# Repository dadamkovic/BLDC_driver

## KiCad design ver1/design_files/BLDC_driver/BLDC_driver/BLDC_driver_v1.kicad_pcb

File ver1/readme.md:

BLDC driver designed around STPIN32F0. This branch will contain 'demo' board design files. The demo board will only have one channel and I will use it to see what does and doesnt work for this design. These notes will be addedin a simple .txt file called v1_notes.txt. In case someone else but me ever stumbles here: 'Hello there random stranger!'

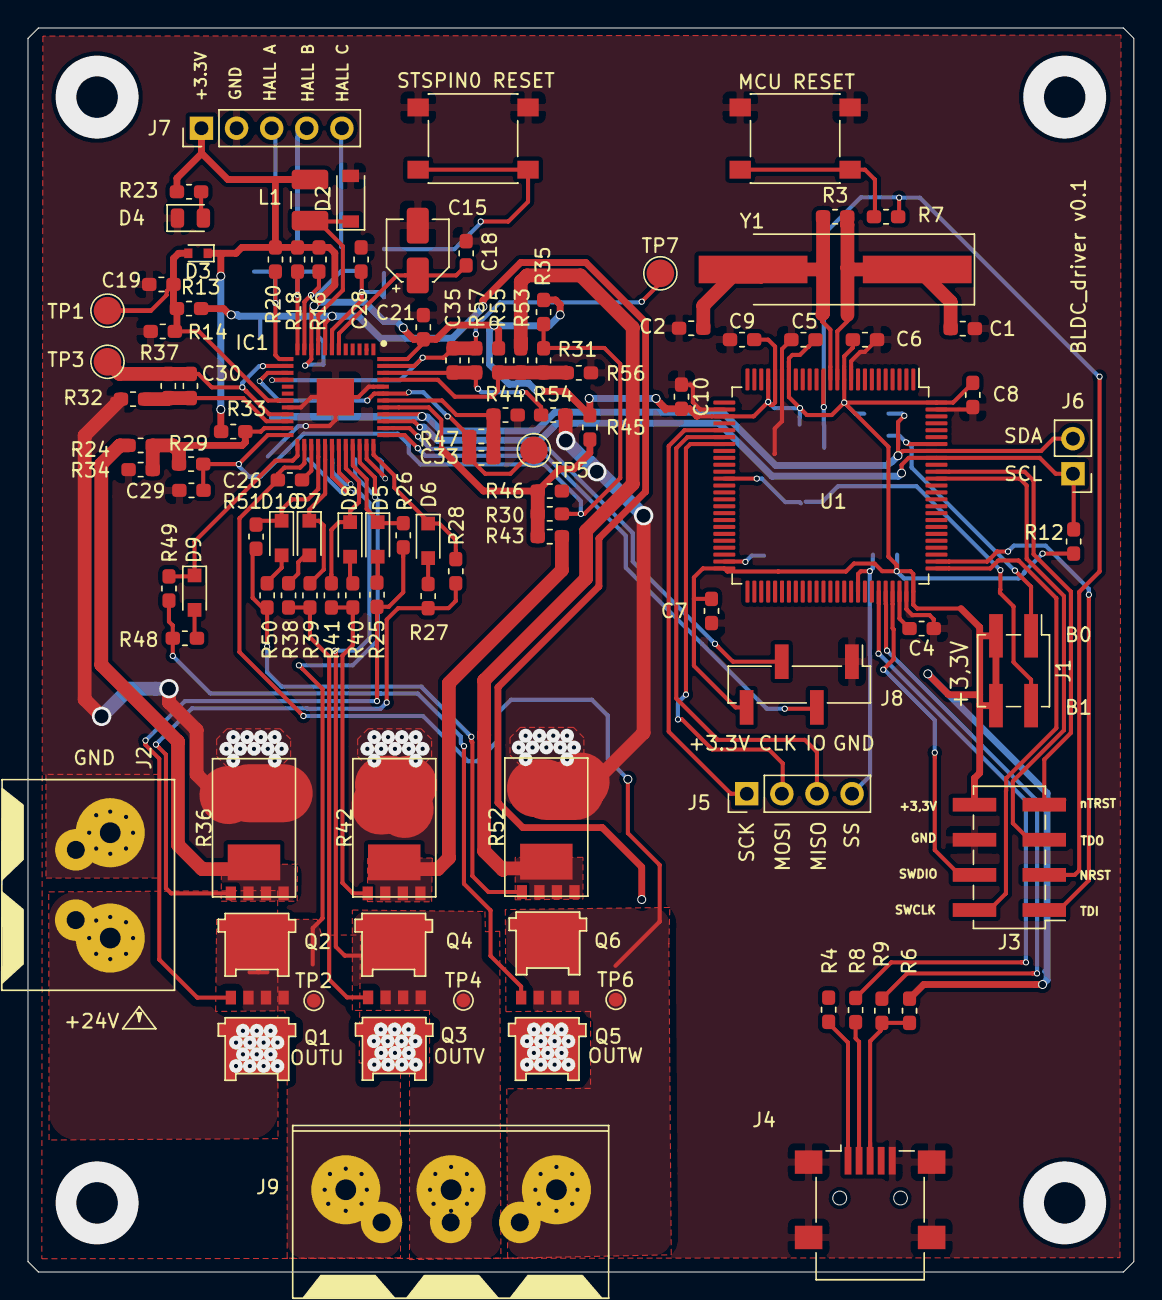
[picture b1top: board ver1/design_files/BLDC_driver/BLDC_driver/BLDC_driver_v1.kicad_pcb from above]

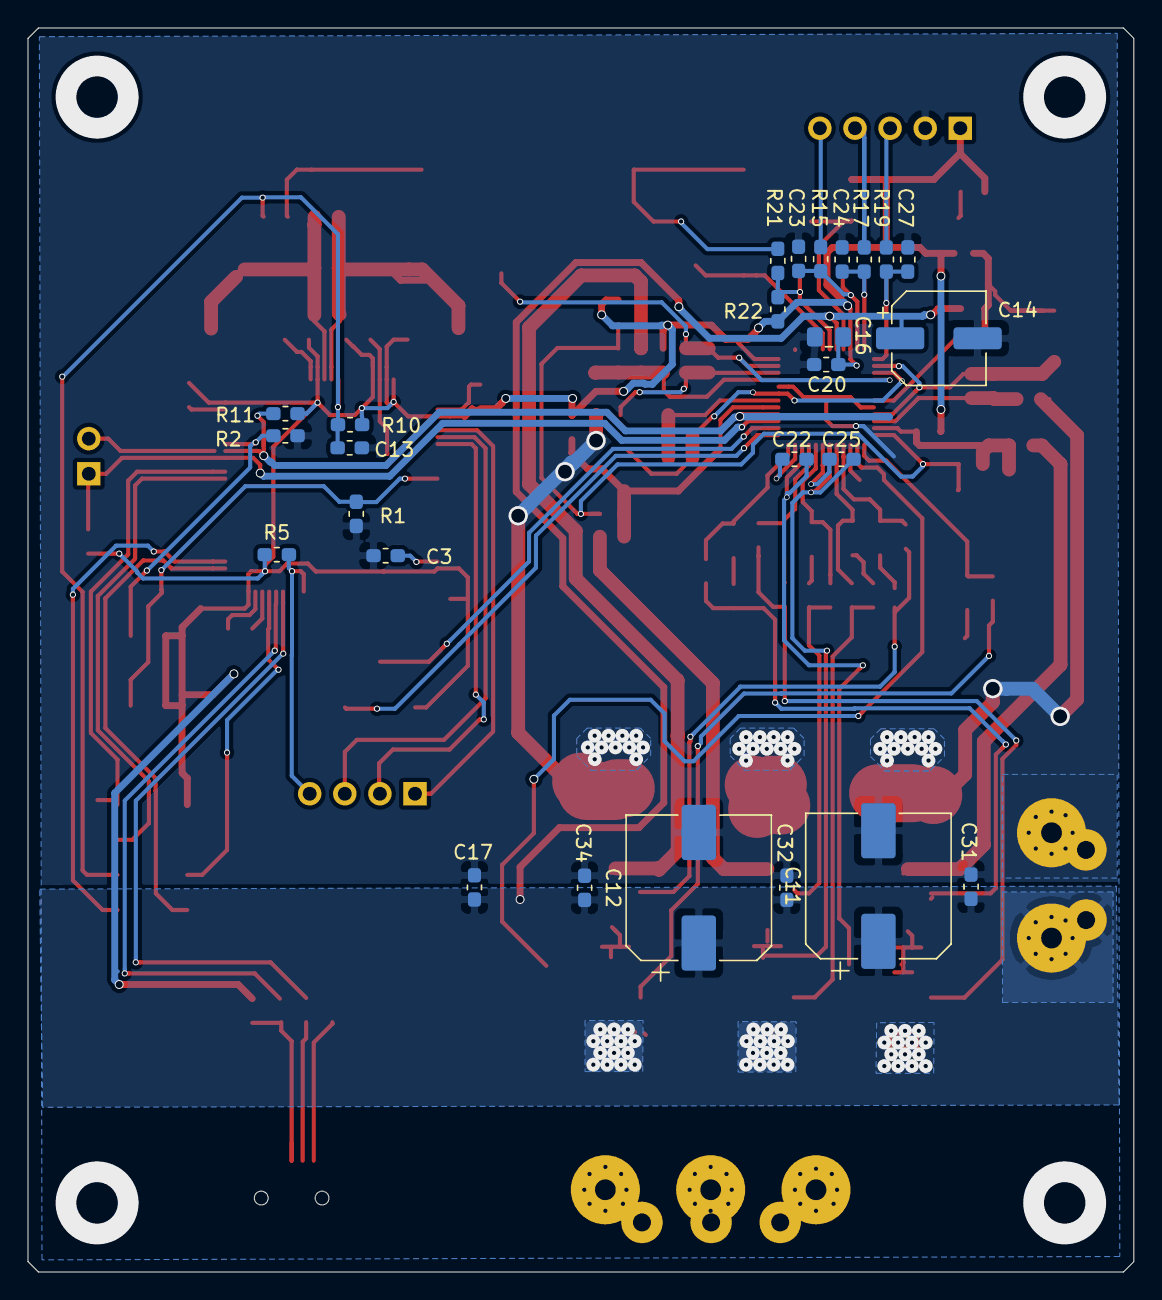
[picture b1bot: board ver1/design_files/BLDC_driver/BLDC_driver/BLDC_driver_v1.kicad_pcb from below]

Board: 2 copper layers, 80.0 x 90.0 mm, 129 parts (26 on the bottom side), 78 nets.

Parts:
C1, C2: 22p; C_0603_1608Metric_Pad1.05x0.95mm_HandSolder
C3: 10uF; C_0603_1608Metric_Pad1.05x0.95mm_HandSolder
C4: C; C_0603_1608Metric_Pad1.05x0.95mm_HandSolder
C5, C6, C7, C8, C9, C10: C_Small; C_0603_1608Metric_Pad1.05x0.95mm_HandSolder
C11: 220uF; CP_Elec_10x10
C12: 47uF; CP_Elec_10x10
C13, C28: 3.3nF; C_0603_1608Metric_Pad1.05x0.95mm_HandSolder
C14: 22uF; CP_Elec_6.3x5.4
C15: 10uF; CP_Elec_4x5.4
C16: 47uF; C_0805_2012Metric_Pad1.15x1.40mm_HandSolder
C17, C30, C31, C32, C33, C34, C35: 220nF; C_0603_1608Metric_Pad1.05x0.95mm_HandSolder
C18, C20, C21, C22, C25, C26: 100nF; C_0603_1608Metric_Pad1.05x0.95mm_HandSolder
C19: 4.7nF; C_0603_1608Metric_Pad1.05x0.95mm_HandSolder
C23, C24, C27: 10pF; C_0603_1608Metric_Pad1.05x0.95mm_HandSolder
C29: 1nF; C_0603_1608Metric_Pad1.05x0.95mm_HandSolder
D2: D_Schottky; D_SOD-123
D3: D_Schottky; D_SOD-523
D4: LED; LED_0805_2012Metric
D5, D6, D7, D8, D9, D10: D; D_SOD-323_HandSoldering
IC1: STSPIN32F0; QFN50P700X700X100-49N-D
J1: Conn_02x02_Counter_Clockwise; PinHeader_2x02_P2.54mm_Vertical_SMD
J2: Screw_Terminal_01x02; Phoenix_7.62_5.08(02x01)
J3: Conn_02x04_Odd_Even; PinHeader_2x04_P2.54mm_Vertical_SMD
J4: USB_OTG; USB_Mini-B_Lumberg_2486_01_Horizontal
J5: Conn_01x04; PinHeader_1x04_P2.54mm_Vertical
J6: Conn_01x02; PinHeader_1x02_P2.54mm_Vertical
J7: Conn_01x05_MountingPin; PinHeader_1x05_P2.54mm_Vertical
J8: Conn_01x04_MountingPin; PinHeader_1x04_P2.54mm_Vertical_SMD_Pin1Left
J9: Screw_Terminal_01x03; Phoenix_7.62mm(03x01)
L1: 22uH; L_1210_3225Metric_Pad1.42x2.65mm_HandSolder
Q1, Q2, Q3, Q4, Q5, Q6: PSMN011-60ML; SO8-FL(N-MOS_Enhancement)
R1, R2: R; R_0603_1608Metric_Pad1.05x0.95mm_HandSolder
R3: 1M; R_0603_1608Metric_Pad1.05x0.95mm_HandSolder
R4, R6: 1K5; R_0603_1608Metric_Pad1.05x0.95mm_HandSolder
R5, R16, R18, R20: 10K; R_0603_1608Metric_Pad1.05x0.95mm_HandSolder
R7, R21: 100R; R_0603_1608Metric_Pad1.05x0.95mm_HandSolder
R8, R9: 22R; R_0603_1608Metric_Pad1.05x0.95mm_HandSolder
R10, R22: 39K; R_0603_1608Metric_Pad1.05x0.95mm_HandSolder
R11, R12, R15, R17, R19: 1K; R_0603_1608Metric_Pad1.05x0.95mm_HandSolder
R13: 169K; R_0603_1608Metric_Pad1.05x0.95mm_HandSolder
R14: 9.31K; R_0603_1608Metric_Pad1.05x0.95mm_HandSolder
R23: 330R; R_0603_1608Metric_Pad1.05x0.95mm_HandSolder
R24, R32, R43, R44, R53, R54: 1.78K; R_0603_1608Metric_Pad1.05x0.95mm_HandSolder
R25, R27, R38, R40, R48, R50: 10R; R_0603_1608Metric_Pad1.05x0.95mm_HandSolder
R26, R28, R39, R41, R49, R51: 62R; R_0603_1608Metric_Pad1.05x0.95mm_HandSolder
R29, R30, R31: 2.2K; R_0603_1608Metric_Pad1.05x0.95mm_HandSolder
R33, R34, R45, R46, R55, R56: 27.4K; R_0603_1608Metric_Pad1.05x0.95mm_HandSolder
R35: 75K; R_0603_1608Metric_Pad1.05x0.95mm_HandSolder
R36, R42, R52: 0R01; R_2512_6432
R37, R47, R57: 13.7K; R_0603_1608Metric_Pad1.05x0.95mm_HandSolder
SW1, SW2: SW_Push; SW_Push_1P1T_NO_6x6mm_H9.5mm
TP1, TP3, TP5, TP7: TestPoint; TestPoint_Pad_D2.0mm
TP2, TP4, TP6: TestPoint; TestPoint_Pad_D1.0mm
U1: STM32F407VETx; LQFP-100_14x14mm_P0.5mm
Y1: 8M; Crystal_SMD_HC49-SD_HandSoldering

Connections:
+3V3: C5.2, C6.2, C7.2, C8.2, C9.2, C10.2, C16.1, C20.1, C21.2, D3.1, IC1.10, IC1.48, J1.3, J1.4, J3.8, J7.1, J8.4, L1.1, R5.2, R6.2, R10.2, R11.1, R12.1, R16.2, R18.2, R20.2, R22.2, R23.1, R33.2, R35.1, R45.2, R55.2, U1.11, U1.19, U1.21, U1.22, U1.28, U1.50, U1.75, U1.100
+12V: C15.1, C18.1, IC1.6
+BATT: C11.1, C12.1, C14.1, C17.1, C31.1, C32.1, C34.1, IC1.8, J2.2, Q1.5, Q3.5, Q5.5, R13.1
/BLDC_A_ctrl/NRST: C28.1, IC1.7, R21.1, R22.1
/BLDC_A_ctrl/OC_COMP: C29.1, IC1.24, R29.1, R30.1, R31.1, R35.2
/BLDC_A_ctrl/OP1N: C30.1, IC1.22, R32.1, R37.2
/BLDC_A_ctrl/OP1O: C30.2, IC1.14, IC1.21, R37.1, TP3.1
/BLDC_A_ctrl/OP1P: IC1.23, R24.2, R29.2, R33.1, R34.2
/BLDC_A_ctrl/OP2N: C33.1, IC1.42, R44.1, R47.2
/BLDC_A_ctrl/OP2O: C33.2, IC1.15, IC1.43, R47.1, TP5.1
/BLDC_A_ctrl/OP2P: IC1.41, R30.2, R43.2, R45.1, R46.2
/BLDC_A_ctrl/OP3N: C35.1, IC1.46, R54.1, R57.2
/BLDC_A_ctrl/OP3O: C35.2, IC1.16, IC1.47, R57.1, TP7.1
/BLDC_A_ctrl/OP3P: IC1.45, R31.2, R53.2, R55.1, R56.2
/BLDC_A_ctrl/PA0: C23.1, IC1.11, R15.1, R16.1
/BLDC_A_ctrl/PA1: C24.1, IC1.12, R17.1, R18.1
/BLDC_A_ctrl/PA2: C27.1, IC1.13, R19.1, R20.1
/BLDC_A_ctrl/PB1: C19.1, D3.2, IC1.19, R13.2, R14.1, TP1.1
/BLDC_A_ctrl/SWD_CLK: IC1.38, J8.3
/BLDC_A_ctrl/SWD_IO: IC1.37, J8.2
/BLDC_A_ctrl/sheet5D69BABD/HSU: D5.1, IC1.33, R26.2
/BLDC_A_ctrl/sheet5D69BABD/HSV: D7.1, IC1.29, R39.2
/BLDC_A_ctrl/sheet5D69BABD/HSW: D9.1, IC1.25, R49.2
/BLDC_A_ctrl/sheet5D69BABD/LSU: D6.1, IC1.36, R28.2
/BLDC_A_ctrl/sheet5D69BABD/LSV: D8.1, IC1.32, R41.2
/BLDC_A_ctrl/sheet5D69BABD/LSW: D10.1, IC1.28, R51.2
/BLDC_A_ctrl/sheet5D69BABD/OUTU: C22.2, IC1.34, J9.1, Q1.1, Q1.2, Q1.3, Q2.5, TP2.1
/BLDC_A_ctrl/sheet5D69BABD/OUTV: C25.2, IC1.30, J9.2, Q3.1, Q3.2, Q3.3, Q4.5, TP4.1
/BLDC_A_ctrl/sheet5D69BABD/OUTW: C26.2, IC1.26, J9.3, Q5.1, Q5.2, Q5.3, Q6.5, TP6.1
/BOOT_0: J1.1, R2.2, U1.94
/BOOT_1: J1.2, R1.2, U1.37
/NRST: C13.1, J3.3, R7.1, R10.1, U1.14
/SCL: IC1.39, J6.1, R12.2, U1.92
/SDA: IC1.40, J6.2, R11.2, U1.93
/SPI1_MISO: J5.3, U1.31
/SPI1_MOSI: J5.2, U1.32
/SPI1_SCK: J5.1, U1.30
/SPI1_SS1: J5.4, R5.1, U1.67
/TCK(SWCLK): J3.2, U1.76
/TDI: J3.1, U1.77
/TDO: J3.5, U1.89
/TMS(SWDIO): J3.4, U1.72
/USB_OTG_FS_DM: R8.1, U1.70
/USB_OTG_FS_DP: R9.1, U1.71
/nTRST: J3.7, U1.90
GNDD: C1.2, C2.2, C3.2, C4.1, C5.1, C6.1, C7.1, C8.1, C9.1, C10.1, C11.2, C12.2, C13.2, C14.2, C15.2, C16.2, C17.2, C18.2, C19.2, C20.2, C21.1, C23.2, C24.2, C27.2, C28.2, C29.2, C31.2, C32.2, C34.2, D2.2, D4.1, IC1.20, IC1.44, IC1.49, J2.1, J3.6, J4.5, J4.6, J7.2, J8.1, R1.1, R2.1, R14.2, R32.2, R34.1, R36.2, R42.2, R44.2, R46.1, R52.2, R54.2, R56.1, SW1.1, SW2.1, U1.10, U1.20, U1.27, U1.74, U1.99
unnamed: C1.1, R3.1, U1.12, Y1.1
unnamed: C2.1, R3.2, U1.13, Y1.2
unnamed: C3.1, U1.49
unnamed: C4.2, U1.73
unnamed: C22.1, IC1.35
unnamed: C25.1, IC1.31
unnamed: C26.1, IC1.27
unnamed: D2.1, IC1.9, L1.2
unnamed: D4.2, R23.2
unnamed: D5.2, R25.2
unnamed: D6.2, R27.2
unnamed: D7.2, R38.2
unnamed: D8.2, R40.2
unnamed: D9.2, R48.2
unnamed: D10.2, R50.2
unnamed: J4.1, R4.1
unnamed: J4.2, R8.2
unnamed: J4.3, R6.1, R9.2
unnamed: J7.3, R19.2
unnamed: J7.4, R17.2
unnamed: J7.5, R15.2
unnamed: Q1.4, R25.1, R26.1
unnamed: Q2.1, Q2.2, Q2.3, R24.1, R36.1
unnamed: Q2.4, R27.1, R28.1
unnamed: Q3.4, R38.1, R39.1
unnamed: Q4.1, Q4.2, Q4.3, R42.1, R43.1
unnamed: Q4.4, R40.1, R41.1
unnamed: Q5.4, R48.1, R49.1
unnamed: Q6.1, Q6.2, Q6.3, R52.1, R53.1
unnamed: Q6.4, R50.1, R51.1
unnamed: R7.2, SW1.2
unnamed: R21.2, SW2.2

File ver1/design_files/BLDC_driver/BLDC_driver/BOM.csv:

Reference, Quantity, Value, Footprint, Datasheet, Description, Height, Manufacturer_Name, Manufacturer_Part_Number, Mouser Part Number, Mouser Price/Stock
C1 C2 ,2,"22p","Capacitor_SMD:C_0603_1608Metric_Pad1.05x0.95mm_HandSolder","~"
C10 C9 C8 C7 C6 C5 ,6,"C_Small","Capacitor_SMD:C_0603_1608Metric_Pad1.05x0.95mm_HandSolder","~"
C11 ,1,"220uF","Capacitor_SMD:CP_Elec_10x10","~"
C12 ,1,"47uF","Capacitor_SMD:CP_Elec_10x10","~"
C13 C28 ,2,"3.3nF","Capacitor_SMD:C_0603_1608Metric_Pad1.05x0.95mm_HandSolder","~"
C14 ,1,"22uF","Capacitor_SMD:CP_Elec_6.3x5.4","~"
C15 ,1,"10uF","Capacitor_SMD:CP_Elec_4x5.4","~"
C16 ,1,"47uF","Capacitor_SMD:C_0805_2012Metric_Pad1.15x1.40mm_HandSolder","~"
C17 C31 C32 C34 C30 C33 C35 ,7,"220nF","Capacitor_SMD:C_0603_1608Metric_Pad1.05x0.95mm_HandSolder","~"
C19 ,1,"4.7nF","Capacitor_SMD:C_0603_1608Metric_Pad1.05x0.95mm_HandSolder","~"
C23 C24 C27 ,3,"10pF","Capacitor_SMD:C_0603_1608Metric_Pad1.05x0.95mm_HandSolder","~"
C25 C26 C21 C20 C18 C22 ,6,"100nF","Capacitor_SMD:C_0603_1608Metric_Pad1.05x0.95mm_HandSolder","~"
C29 ,1,"1nF","Capacitor_SMD:C_0603_1608Metric_Pad1.05x0.95mm_HandSolder","~"
C3 ,1,"10uF","Capacitor_SMD:C_0603_1608Metric_Pad1.05x0.95mm_HandSolder","~"
C4 ,1,"C","Capacitor_SMD:C_0603_1608Metric_Pad1.05x0.95mm_HandSolder","~"
D2 ,1,"D_Schottky","Diode_SMD:D_SOD-123","~"
D3 ,1,"D_Schottky","Diode_SMD:D_SOD-523","~"
D4 ,1,"LED","LED_SMD:LED_0805_2012Metric","~"
D5 D6 D7 D8 D9 D10 ,6,"D","Diode_SMD:D_SOD-323_HandSoldering","~"
IC1 ,1,"STSPIN32F0","SamacSys_Parts:QFN50P700X700X100-49N-D","https://componentsearchengine.com/Datasheets/1/STSPIN32F0.pdf","Motor / Motion / Ignition Controllers & Drivers Advance BLDC Contrlr w/Embedded STM32 MCU","1","STMicroelectronics","STSPIN32F0","511-STSPIN32F0","https://www.mouser.com/Search/Refine.aspx?Keyword=511-STSPIN32F0"
J1 ,1,"Conn_02x02_Counter_Clockwise","Connector_PinHeader_2.54mm:PinHeader_2x02_P2.54mm_Vertical_SMD","~"
J2 ,1,"Screw_Terminal_01x02","my_misc:Phoenix_7.62_5.08(02x01)","~"
J3 ,1,"Conn_02x04_Odd_Even","Connector_PinHeader_2.54mm:PinHeader_2x04_P2.54mm_Vertical_SMD","~"
J4 ,1,"USB_OTG","Connector_USB:USB_Mini-B_Lumberg_2486_01_Horizontal"," ~"
J5 ,1,"Conn_01x04","Connector_PinHeader_2.54mm:PinHeader_1x04_P2.54mm_Vertical","~"
J6 ,1,"Conn_01x02","Connector_PinHeader_2.54mm:PinHeader_1x02_P2.54mm_Vertical","~"
J7 ,1,"Conn_01x05_MountingPin","Connector_PinHeader_2.54mm:PinHeader_1x05_P2.54mm_Vertical","~"
J8 ,1,"Conn_01x04_MountingPin","Connector_PinHeader_2.54mm:PinHeader_1x04_P2.54mm_Vertical_SMD_Pin1Left","~"
J9 ,1,"Screw_Terminal_01x03","my_misc:Phoenix_7.62mm(03x01)","~"
L1 ,1,"22uH","Inductor_SMD:L_1210_3225Metric_Pad1.42x2.65mm_HandSolder","~"
Q1 Q2 Q3 Q4 Q6 Q5 ,6,"PSMN011-60ML","my_misc:SO8-FL(N-MOS_Enhancement)","http://www.jaolen.com/images/pdf/QM6006D.pdf"
R1 R2 ,2,"R","Resistor_SMD:R_0603_1608Metric_Pad1.05x0.95mm_HandSolder","~"
R10 R22 ,2,"39K","Resistor_SMD:R_0603_1608Metric_Pad1.05x0.95mm_HandSolder","~"
R11 R12 R15 R17 R19 ,5,"1K","Resistor_SMD:R_0603_1608Metric_Pad1.05x0.95mm_HandSolder","~"
R13 ,1,"169K","Resistor_SMD:R_0603_1608Metric_Pad1.05x0.95mm_HandSolder","~"
R14 ,1,"9.31K","Resistor_SMD:R_0603_1608Metric_Pad1.05x0.95mm_HandSolder","~"
R23 ,1,"330R","Resistor_SMD:R_0603_1608Metric_Pad1.05x0.95mm_HandSolder","~"
R24 R32 R43 R44 R53 R54 ,6,"1.78K","Resistor_SMD:R_0603_1608Metric_Pad1.05x0.95mm_HandSolder","~"
R25 R27 R38 R40 R48 R50 ,6,"10R","Resistor_SMD:R_0603_1608Metric_Pad1.05x0.95mm_HandSolder","~"
R26 R28 R39 R41 R49 R51 ,6,"62R","Resistor_SMD:R_0603_1608Metric_Pad1.05x0.95mm_HandSolder","~"
R29 R30 R31 ,3,"2.2K","Resistor_SMD:R_0603_1608Metric_Pad1.05x0.95mm_HandSolder","~"
R3 ,1,"1M","Resistor_SMD:R_0603_1608Metric_Pad1.05x0.95mm_HandSolder","~"
R33 R34 R45 R46 R55 R56 ,6,"27.4K","Resistor_SMD:R_0603_1608Metric_Pad1.05x0.95mm_HandSolder","~"
R35 ,1,"75K","Resistor_SMD:R_0603_1608Metric_Pad1.05x0.95mm_HandSolder","~"
R37 R47 R57 ,3,"13.7K","Resistor_SMD:R_0603_1608Metric_Pad1.05x0.95mm_HandSolder","~"
R42 R36 R52 ,3,"0R01","Resistor_SMD:R_2512_6332Metric_Pad1.52x3.35mm_HandSolder","~"
R5 R16 R18 R20 ,4,"10K","Resistor_SMD:R_0603_1608Metric_Pad1.05x0.95mm_HandSolder","~"
R6 R4 ,2,"1K5","Resistor_SMD:R_0603_1608Metric_Pad1.05x0.95mm_HandSolder","~"
R7 R21 ,2,"100R","Resistor_SMD:R_0603_1608Metric_Pad1.05x0.95mm_HandSolder","~"
R9 R8 ,2,"22R","Resistor_SMD:R_0603_1608Metric_Pad1.05x0.95mm_HandSolder","~"
SW1 SW2 ,2,"SW_Push","Button_Switch_SMD:SW_Push_1P1T_NO_6x6mm_H9.5mm","~"
TP1 TP3 TP5 TP7 ,4,"TestPoint","TestPoint:TestPoint_Pad_D2.0mm","~"
TP2 TP4 TP6 ,3,"TestPoint","TestPoint:TestPoint_Pad_D1.0mm","~"
U1 ,1,"STM32F407VETx","Package_QFP:LQFP-100_14x14mm_P0.5mm","http://www.st.com/st-web-ui/static/active/en/resource/techni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"
Y1 ,1,"8M","Crystal:Crystal_SMD_HC49-SD_HandSoldering","~"

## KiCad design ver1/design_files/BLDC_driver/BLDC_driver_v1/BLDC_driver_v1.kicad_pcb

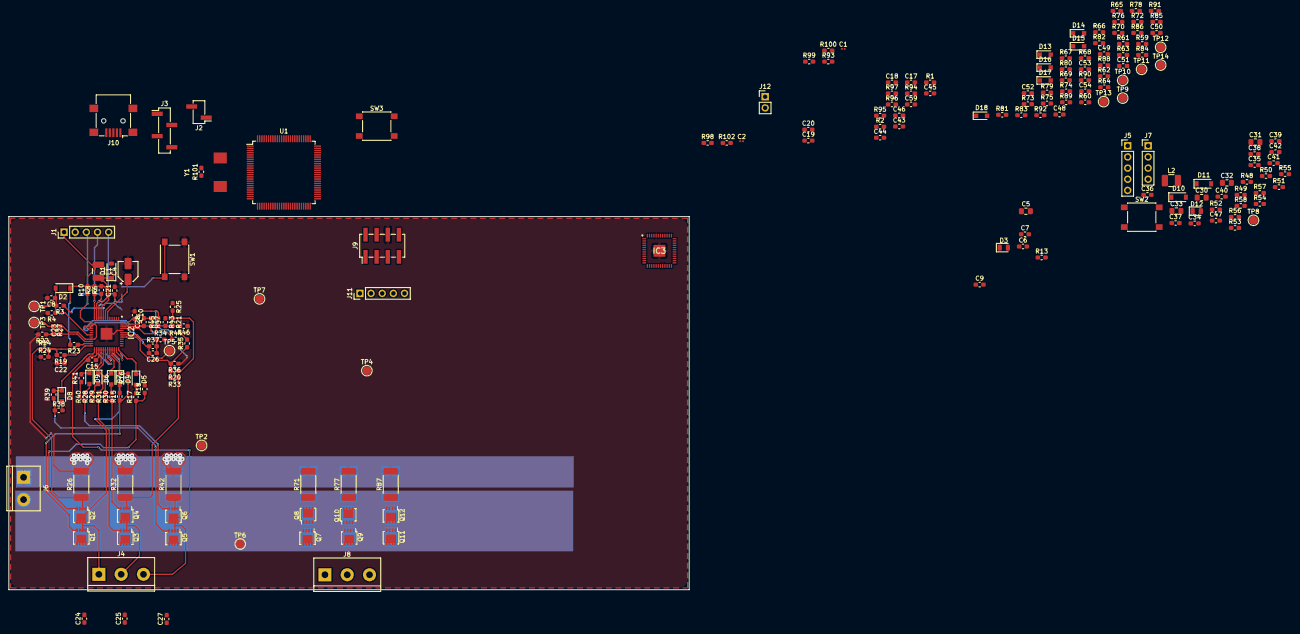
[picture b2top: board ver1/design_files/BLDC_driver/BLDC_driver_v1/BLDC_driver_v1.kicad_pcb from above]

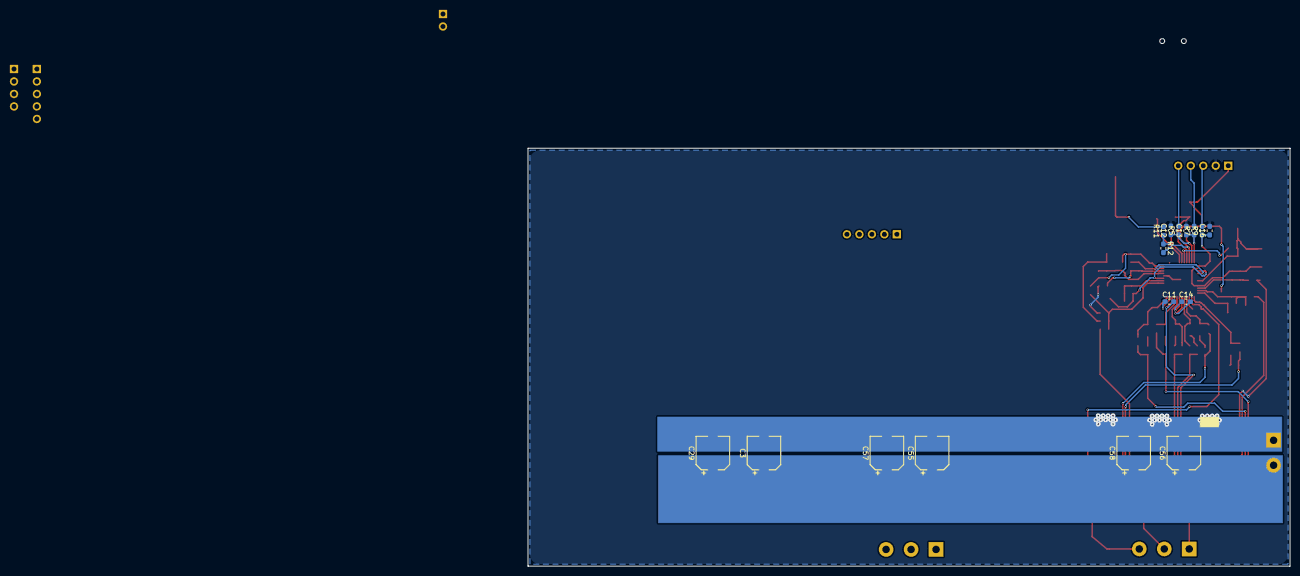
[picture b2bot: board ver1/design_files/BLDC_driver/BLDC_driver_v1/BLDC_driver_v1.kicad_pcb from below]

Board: 2 copper layers, 155.0 x 85.0 mm, 226 parts (16 on the bottom side), 128 nets.

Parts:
C1, C2: 22p; C_0201_0603Metric
C3, C29: 22uF; CP_Elec_6.3x7.7
C4: 10uF; CP_Elec_4x5.4
C5, C31: 47uF; C_0805_2012Metric_Pad1.15x1.40mm_HandSolder
C6, C23, C24, C25, C26, C27, C28, C49, C50, C51, C52, C53, C54: 220nF; C_0603_1608Metric_Pad1.05x0.95mm_HandSolder
C7, C9, C10, C11, C14, C15, C35, C36, C37, C40, C41: 100nF; C_0603_1608Metric_Pad1.05x0.95mm_HandSolder
C8, C34: 4.7nF; C_0603_1608Metric_Pad1.05x0.95mm_HandSolder
C12, C13, C16, C38, C39, C42: 10pF; C_0603_1608Metric_Pad1.05x0.95mm_HandSolder
C17: 10uF; C_0603_1608Metric_Pad1.05x0.95mm_HandSolder
C18: C; C_0603_1608Metric_Pad1.05x0.95mm_HandSolder
C19, C20, C43, C44, C45, C46: C_Small; C_0603_1608Metric_Pad1.05x0.95mm_HandSolder
C21, C47, C59: 3.3nF; C_0603_1608Metric_Pad1.05x0.95mm_HandSolder
C22, C48: 1nF; C_0603_1608Metric_Pad1.05x0.95mm_HandSolder
C30: 22uF; C_0805_2012Metric_Pad1.15x1.40mm_HandSolder
C32, C33: 220nF; C_0805_2012Metric_Pad1.15x1.40mm_HandSolder
C55, C56: 22uF; CP_Elec_6.3x5.4
C57, C58: 47uF; CP_Elec_6.3x5.4
D1, D2, D10, D11: D_Schottky; D_SOD-123
D3, D12: LED; LED_0805_2012Metric
D4, D5, D6, D7, D8, D9, D13, D14, D15, D16, D17, D18: D; D_SOD-323_HandSoldering
IC2, IC3: STSPIN32F0; QFN50P700X700X100-49N-D
J1, J5: Conn_01x05_MountingPin; PinHeader_1x05_P2.54mm_Vertical
J2: Conn_01x02; PinHeader_1x02_P2.54mm_Vertical_SMD_Pin1Left
J3: Conn_01x04_MountingPin; PinHeader_1x04_P2.54mm_Vertical_SMD_Pin1Left
J4, J8: Screw_Terminal_01x03; TerminalBlock_bornier-3_P5.08mm
J6: Screw_Terminal_01x02; TerminalBlock_bornier-2_P5.08mm
J7: Conn_01x04_MountingPin; PinHeader_1x04_P2.54mm_Vertical
J9: Conn_02x04_Odd_Even; PinHeader_2x04_P2.54mm_Vertical_SMD
J10: USB_OTG; USB_Mini-B_Lumberg_2486_01_Horizontal
J11: Conn_01x05; PinHeader_1x05_P2.54mm_Vertical
J12: Conn_01x02; PinHeader_1x02_P2.54mm_Vertical
L1, L2: 22uH; L_1210_3225Metric_Pad1.42x2.65mm_HandSolder
Q1, Q2, Q3, Q4, Q5, Q6, Q7, Q8, Q9, Q10, Q11, Q12: PSMN011-60ML; LFPAK33
R1, R2, R5, R7, R9, R50, R52, R54: 1K; R_0603_1608Metric_Pad1.05x0.95mm_HandSolder
R3, R48: 169K; R_0603_1608Metric_Pad1.05x0.95mm_HandSolder
R4, R49: 9.31K; R_0603_1608Metric_Pad1.05x0.95mm_HandSolder
R6, R8, R10, R51, R53, R55, R102: 10K; R_0603_1608Metric_Pad1.05x0.95mm_HandSolder
R11, R56, R98: 100R; R_0603_1608Metric_Pad1.05x0.95mm_HandSolder
R12, R57, R101: 39K; R_0603_1608Metric_Pad1.05x0.95mm_HandSolder
R13, R58: 330R; R_0603_1608Metric_Pad1.05x0.95mm_HandSolder
R14, R22, R33, R34, R43, R44, R59, R67, R78, R79, R88, R89: 1.78K; R_0603_1608Metric_Pad1.05x0.95mm_HandSolder
R15, R17, R28, R30, R38, R40, R60, R62, R73, R75, R83, R85: 10R; R_0603_1608Metric_Pad1.05x0.95mm_HandSolder
R16, R18, R29, R31, R39, R41, R61, R63, R74, R76, R84, R86: 62R; R_0603_1608Metric_Pad1.05x0.95mm_HandSolder
R19, R20, R21, R64, R65, R66: 2.2K; R_0603_1608Metric_Pad1.05x0.95mm_HandSolder
R23, R24, R35, R36, R45, R46, R68, R69, R80, R81, R90, R91: 27.4K; R_0603_1608Metric_Pad1.05x0.95mm_HandSolder
R25, R70: 75K; R_0603_1608Metric_Pad1.05x0.95mm_HandSolder
R26, R32, R42, R71, R77, R87: 0R01; R_2512_6332Metric_Pad1.52x3.35mm_HandSolder
R27, R37, R47, R72, R82, R92: 13.7K; R_0603_1608Metric_Pad1.05x0.95mm_HandSolder
R93, R94: R; R_0603_1608Metric_Pad1.05x0.95mm_HandSolder
R95: 1M; R_0603_1608Metric_Pad1.05x0.95mm_HandSolder
R96, R97: 1K5; R_0603_1608Metric_Pad1.05x0.95mm_HandSolder
R99, R100: 22R; R_0603_1608Metric_Pad1.05x0.95mm_HandSolder
SW1, SW2, SW3: SW_Push; SW_Push_1P1T_NO_6x6mm_H9.5mm
TP1, TP2, TP3, TP4, TP5, TP6, TP7, TP8, TP9, TP10, TP11, TP12, TP13, TP14: TestPoint; TestPoint_Pad_D2.0mm
U1: STM32F407VETx; LQFP-100_14x14mm_P0.5mm
Y1: 8M; oscilator_8.0x4.5(mm)

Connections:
+3V3: C5.1, C9.1, C10.2, C19.2, C20.2, C31.1, C35.1, C36.2, C43.2, C44.2, C45.2, C46.2, D2.1, D11.1, IC2.10, IC2.48, IC3.10, IC3.48, J1.1, J3.4, J7.4, J9.8, L1.1, L2.1, R1.1, R2.1, R6.2, R8.2, R10.2, R12.2, R13.1, R23.2, R25.1, R35.2, R45.2, R51.2, R53.2, R55.2, R57.2, R58.1, R68.2, R70.1, R80.2, R90.2, R97.2, R101.2, R102.2, U1.11, U1.19, U1.21, U1.22, U1.28, U1.50, U1.75, U1.100
+12V: C4.1, C7.1, C30.1, C33.1, IC2.6, IC3.6
+BATT: C3.1, C6.1, C24.1, C25.1, C27.1, C29.1, C32.1, C50.1, C51.1, C53.1, C55.1, C56.1, C57.1, C58.1, IC2.8, IC3.8, J6.2, Q1.5, Q3.5, Q5.5, Q7.5, Q9.5, Q11.5, R3.1, R48.1
/BLDC_A_ctrl/NRST: C21.1, IC2.7, R11.1, R12.1
/BLDC_A_ctrl/OC_COMP: C22.1, IC2.24, R19.1, R20.1, R21.1, R25.2
/BLDC_A_ctrl/OP1N: C23.1, IC2.22, R22.1, R27.2
/BLDC_A_ctrl/OP1O: C23.2, IC2.14, IC2.21, R27.1, TP3.1
/BLDC_A_ctrl/OP1P: IC2.23, R14.2, R19.2, R23.1, R24.2
/BLDC_A_ctrl/OP2N: C26.1, IC2.42, R34.1, R37.2
/BLDC_A_ctrl/OP2O: C26.2, IC2.15, IC2.43, R37.1, TP5.1
/BLDC_A_ctrl/OP2P: IC2.41, R20.2, R33.2, R35.1, R36.2
/BLDC_A_ctrl/OP3N: C28.1, IC2.46, R44.1, R47.2
/BLDC_A_ctrl/OP3O: C28.2, IC2.16, IC2.47, R47.1, TP7.1
/BLDC_A_ctrl/OP3P: IC2.45, R21.2, R43.2, R45.1, R46.2
/BLDC_A_ctrl/PA0: C12.1, IC2.11, R5.1, R6.1
/BLDC_A_ctrl/PA1: C13.1, IC2.12, R7.1, R8.1
/BLDC_A_ctrl/PA2: C16.1, IC2.13, R9.1, R10.1
/BLDC_A_ctrl/PB1: C8.1, D2.2, IC2.19, R3.2, R4.1, TP1.1
/BLDC_A_ctrl/SWD_CLK: IC2.38, J3.3
/BLDC_A_ctrl/SWD_IO: IC2.37, J3.2
/BLDC_A_ctrl/sheet5D69BABD/HSU: D4.1, IC2.33, R16.2
/BLDC_A_ctrl/sheet5D69BABD/HSV: D6.1, IC2.29, R29.2
/BLDC_A_ctrl/sheet5D69BABD/HSW: D8.1, IC2.25, R39.2
/BLDC_A_ctrl/sheet5D69BABD/LSU: D5.1, IC2.36, R18.2
/BLDC_A_ctrl/sheet5D69BABD/LSV: D7.1, IC2.32, R31.2
/BLDC_A_ctrl/sheet5D69BABD/LSW: D9.1, IC2.28, R41.2
/BLDC_A_ctrl/sheet5D69BABD/OUTU: C11.2, IC2.34, J4.1, Q1.1, Q1.2, Q1.3, Q2.5, TP2.1
/BLDC_A_ctrl/sheet5D69BABD/OUTV: C14.2, IC2.30, J4.2, Q3.1, Q3.2, Q3.3, Q4.5, TP4.1
/BLDC_A_ctrl/sheet5D69BABD/OUTW: C15.2, IC2.26, J4.3, Q5.1, Q5.2, Q5.3, Q6.5, TP6.1
/BLDC_B_ctrl/NRST: C47.1, IC3.7, R56.1, R57.1
/BLDC_B_ctrl/OC_COMP: C48.1, IC3.24, R64.1, R65.1, R66.1, R70.2
/BLDC_B_ctrl/OP1N: C49.1, IC3.22, R67.1, R72.2
/BLDC_B_ctrl/OP1O: C49.2, IC3.14, IC3.21, R72.1, TP10.1
/BLDC_B_ctrl/OP1P: IC3.23, R59.2, R64.2, R68.1, R69.2
/BLDC_B_ctrl/OP2N: C52.1, IC3.42, R79.1, R82.2
/BLDC_B_ctrl/OP2O: C52.2, IC3.15, IC3.43, R82.1, TP12.1
/BLDC_B_ctrl/OP2P: IC3.41, R65.2, R78.2, R80.1, R81.2
/BLDC_B_ctrl/OP3N: C54.1, IC3.46, R89.1, R92.2
/BLDC_B_ctrl/OP3O: C54.2, IC3.16, IC3.47, R92.1, TP14.1
/BLDC_B_ctrl/OP3P: IC3.45, R66.2, R88.2, R90.1, R91.2
/BLDC_B_ctrl/PA0: C38.1, IC3.11, R50.1, R51.1
/BLDC_B_ctrl/PA1: C39.1, IC3.12, R52.1, R53.1
/BLDC_B_ctrl/PA2: C42.1, IC3.13, R54.1, R55.1
/BLDC_B_ctrl/PB1: C34.1, D11.2, IC3.19, R48.2, R49.1, TP8.1
/BLDC_B_ctrl/SWD_CLK: IC3.38, J7.3
/BLDC_B_ctrl/SWD_IO: IC3.37, J7.2
/BLDC_B_ctrl/sheet5D640490/HSU: D13.1, IC3.33, R61.2
/BLDC_B_ctrl/sheet5D640490/HSV: D15.1, IC3.29, R74.2
/BLDC_B_ctrl/sheet5D640490/HSW: D17.1, IC3.25, R84.2
/BLDC_B_ctrl/sheet5D640490/LSU: D14.1, IC3.36, R63.2
/BLDC_B_ctrl/sheet5D640490/LSV: D16.1, IC3.32, R76.2
/BLDC_B_ctrl/sheet5D640490/LSW: D18.1, IC3.28, R86.2
/BLDC_B_ctrl/sheet5D640490/OUTU: C37.2, IC3.34, J8.1, Q7.1, Q7.2, Q7.3, Q8.5, TP9.1
/BLDC_B_ctrl/sheet5D640490/OUTV: C40.2, IC3.30, J8.2, Q9.1, Q9.2, Q9.3, Q10.5, TP11.1
/BLDC_B_ctrl/sheet5D640490/OUTW: C41.2, IC3.26, J8.3, Q11.1, Q11.2, Q11.3, Q12.5, TP13.1
/BOOT_0: J2.1, R94.2, U1.94
/BOOT_1: J2.2, R93.2, U1.37
/NRST: C59.1, J9.3, R98.1, R101.1, U1.14
/SCL: IC2.39, IC3.39, J12.1, R2.2, U1.92
/SDA: IC2.40, IC3.40, J12.2, R1.2, U1.93
/SPI1_MISO: J11.3, U1.31
/SPI1_MOSI: J11.2, U1.32
/SPI1_SCK: J11.1, U1.30
/SPI1_SS1: J11.4, R102.1, U1.67
/TCK(SWCLK): J9.2, U1.76
/TDI: J9.1, U1.77
/TDO: J9.5, U1.89
/TMS(SWDIO): J9.4, U1.72
/USB_OTG_FS_DM: R99.1, U1.70
/USB_OTG_FS_DP: R100.1, U1.71
/nTRST: J9.7, U1.90
GNDD: C1.2, C2.2, C3.2, C4.2, C5.2, C6.2, C7.2, C8.2, C9.2, C10.1, C12.2, C13.2, C16.2, C17.2, C18.1, C19.1, C20.1, C21.2, C22.2, C24.2, C25.2, C27.2, C29.2, C30.2, C31.2, C32.2, C33.2, C34.2, C35.2, C36.1, C38.2, C39.2, C42.2, C43.1, C44.1, C45.1, C46.1, C47.2, C48.2, C50.2, C51.2, C53.2, C55.2, C56.2, C57.2, C58.2, C59.2, D1.2, D3.1, D10.2, D12.1, IC2.20, IC2.44, IC2.49, IC3.20, IC3.44, IC3.49, J1.2, J3.1, J5.2, J6.1, J7.1, J9.6, J10.5, J10.6, R4.2, R22.2, R24.1, R26.2, R32.2, R34.2, R36.1, R42.2, R44.2, R46.1, R49.2, R67.2, R69.1, R71.2, R77.2, R79.2, R81.1, R87.2, R89.2, R91.1, R93.1, R94.1, SW1.1, SW2.1, SW3.1, U1.10, U1.20, U1.27, U1.74, U1.99
unnamed: C1.1, R95.1, U1.12, Y1.1
unnamed: C2.1, R95.2, U1.13, Y1.2
unnamed: C11.1, IC2.35
unnamed: C14.1, IC2.31
unnamed: C15.1, IC2.27
unnamed: C17.1, U1.49
unnamed: C18.2, U1.73
unnamed: C37.1, IC3.35
unnamed: C40.1, IC3.31
unnamed: C41.1, IC3.27
unnamed: D1.1, IC2.9, L1.2
unnamed: D3.2, R13.2
unnamed: D4.2, R15.2
unnamed: D5.2, R17.2
unnamed: D6.2, R28.2
unnamed: D7.2, R30.2
unnamed: D8.2, R38.2
unnamed: D9.2, R40.2
unnamed: D10.1, IC3.9, L2.2
unnamed: D12.2, R58.2
unnamed: D13.2, R60.2
unnamed: D14.2, R62.2
unnamed: D15.2, R73.2
unnamed: D16.2, R75.2
unnamed: D17.2, R83.2
unnamed: D18.2, R85.2
unnamed: J1.3, R9.2
unnamed: J1.4, R7.2
unnamed: J1.5, R5.2
unnamed: J5.3, R54.2
unnamed: J5.4, R52.2
unnamed: J5.5, R50.2
unnamed: J10.1, R96.1
unnamed: J10.2, R99.2
unnamed: J10.3, R97.1, R100.2
unnamed: Q1.4, R15.1, R16.1
unnamed: Q2.1, Q2.2, Q2.3, R14.1, R26.1
unnamed: Q2.4, R17.1, R18.1
unnamed: Q3.4, R28.1, R29.1
unnamed: Q4.1, Q4.2, Q4.3, R32.1, R33.1
unnamed: Q4.4, R30.1, R31.1
unnamed: Q5.4, R38.1, R39.1
unnamed: Q6.1, Q6.2, Q6.3, R42.1, R43.1
unnamed: Q6.4, R40.1, R41.1
unnamed: Q7.4, R60.1, R61.1
unnamed: Q8.1, Q8.2, Q8.3, R59.1, R71.1
unnamed: Q8.4, R62.1, R63.1
unnamed: Q9.4, R73.1, R74.1
unnamed: Q10.1, Q10.2, Q10.3, R77.1, R78.1
unnamed: Q10.4, R75.1, R76.1
unnamed: Q11.4, R83.1, R84.1
unnamed: Q12.1, Q12.2, Q12.3, R87.1, R88.1
unnamed: Q12.4, R85.1, R86.1
unnamed: R11.2, SW1.2
unnamed: R56.2, SW2.2
unnamed: R98.2, SW3.2

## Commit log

2019-10-13 Initial commit with not much in it except PCB stuff and some demo program stubs for testing hardware.
2019-10-13 Various documentation and other useful documents I am using as a reference.
2019-10-13 Added readme
